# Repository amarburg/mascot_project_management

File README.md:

This repo provides project- and system-level information about the MaSCOT project.  For a high-level overview, see [my blog](http://faculty.washington.edu/amarburg/site/mascot/)

Introduction
------------

The 2016 SEG IR&D Stereo Camera project is supporting the development of a low-cost
stereo camera head in a shallow water enclosure.   The sensor head
will provide stereo video including a dense depth estimate and will include
sufficient on-board processing power for realtime 3D reconstruction.

The sensor head consists of a [Stereolabs
Zed](https://www.stereolabs.com/zed/specs/) USB3 stereo camera and an [NVIdia
Jetson TX1](http://www.nvidia.com/object/jetson-tx1-module.html) embedded
computer.   The Zed consists of a two-camera USB3 sensor unit and a proprietary
set of software libraries for interfacing with the sensor and generating
realtime dense stereo.  These libraries are accelerated using NVidia's CUDA
technology.  The Jetson TX1 computer module contains four 64-bit ARM processor
cores as well as a 256-CUDA core GPU, which allows the Jetson TX1 to run the Zed
processing library.

The Jetson itself lives on a small (approx. credit card) carrier board, but for
development purposes a mini-itx 5" x 5" motherboard is provided which includes a
number of standardized connectors (SATA, Ethernet, SD card, PCI-E, mini-PCI-E)
as well as expansion and debug pin headers.   While the 5"x5" form factor is
somewhat awkward for packaging, the motherboard greatly simplifies the
bootstrapping of new projects.   Given that complete schematics for the
motherboard are available, more application-specific host boards are
theoretically possible.

The underwater enclosure package has a single Subconn 8-pin connector which
provides Cat6 UTP to the sensor head.  This cabling provides gigabit ethernet as
well as 60W power-over-ethernet (PoE).  Note 60W PoE is non-standard. This
connector allows reuse of existing subsea ethernet cables but prevents
supplemental functions going over the same cable (unless we put an Ethernet hub
in the box).      The package also includes two [BlueRobotic Lumen
1](https://www.bluerobotics.com/store/electronics/lumen-light-r1/) submersible
LED lights.

## Other repos

  * https://github.com/amarburg/mascot_companion_board contains schematics and firmware for the Jetson "companion board."

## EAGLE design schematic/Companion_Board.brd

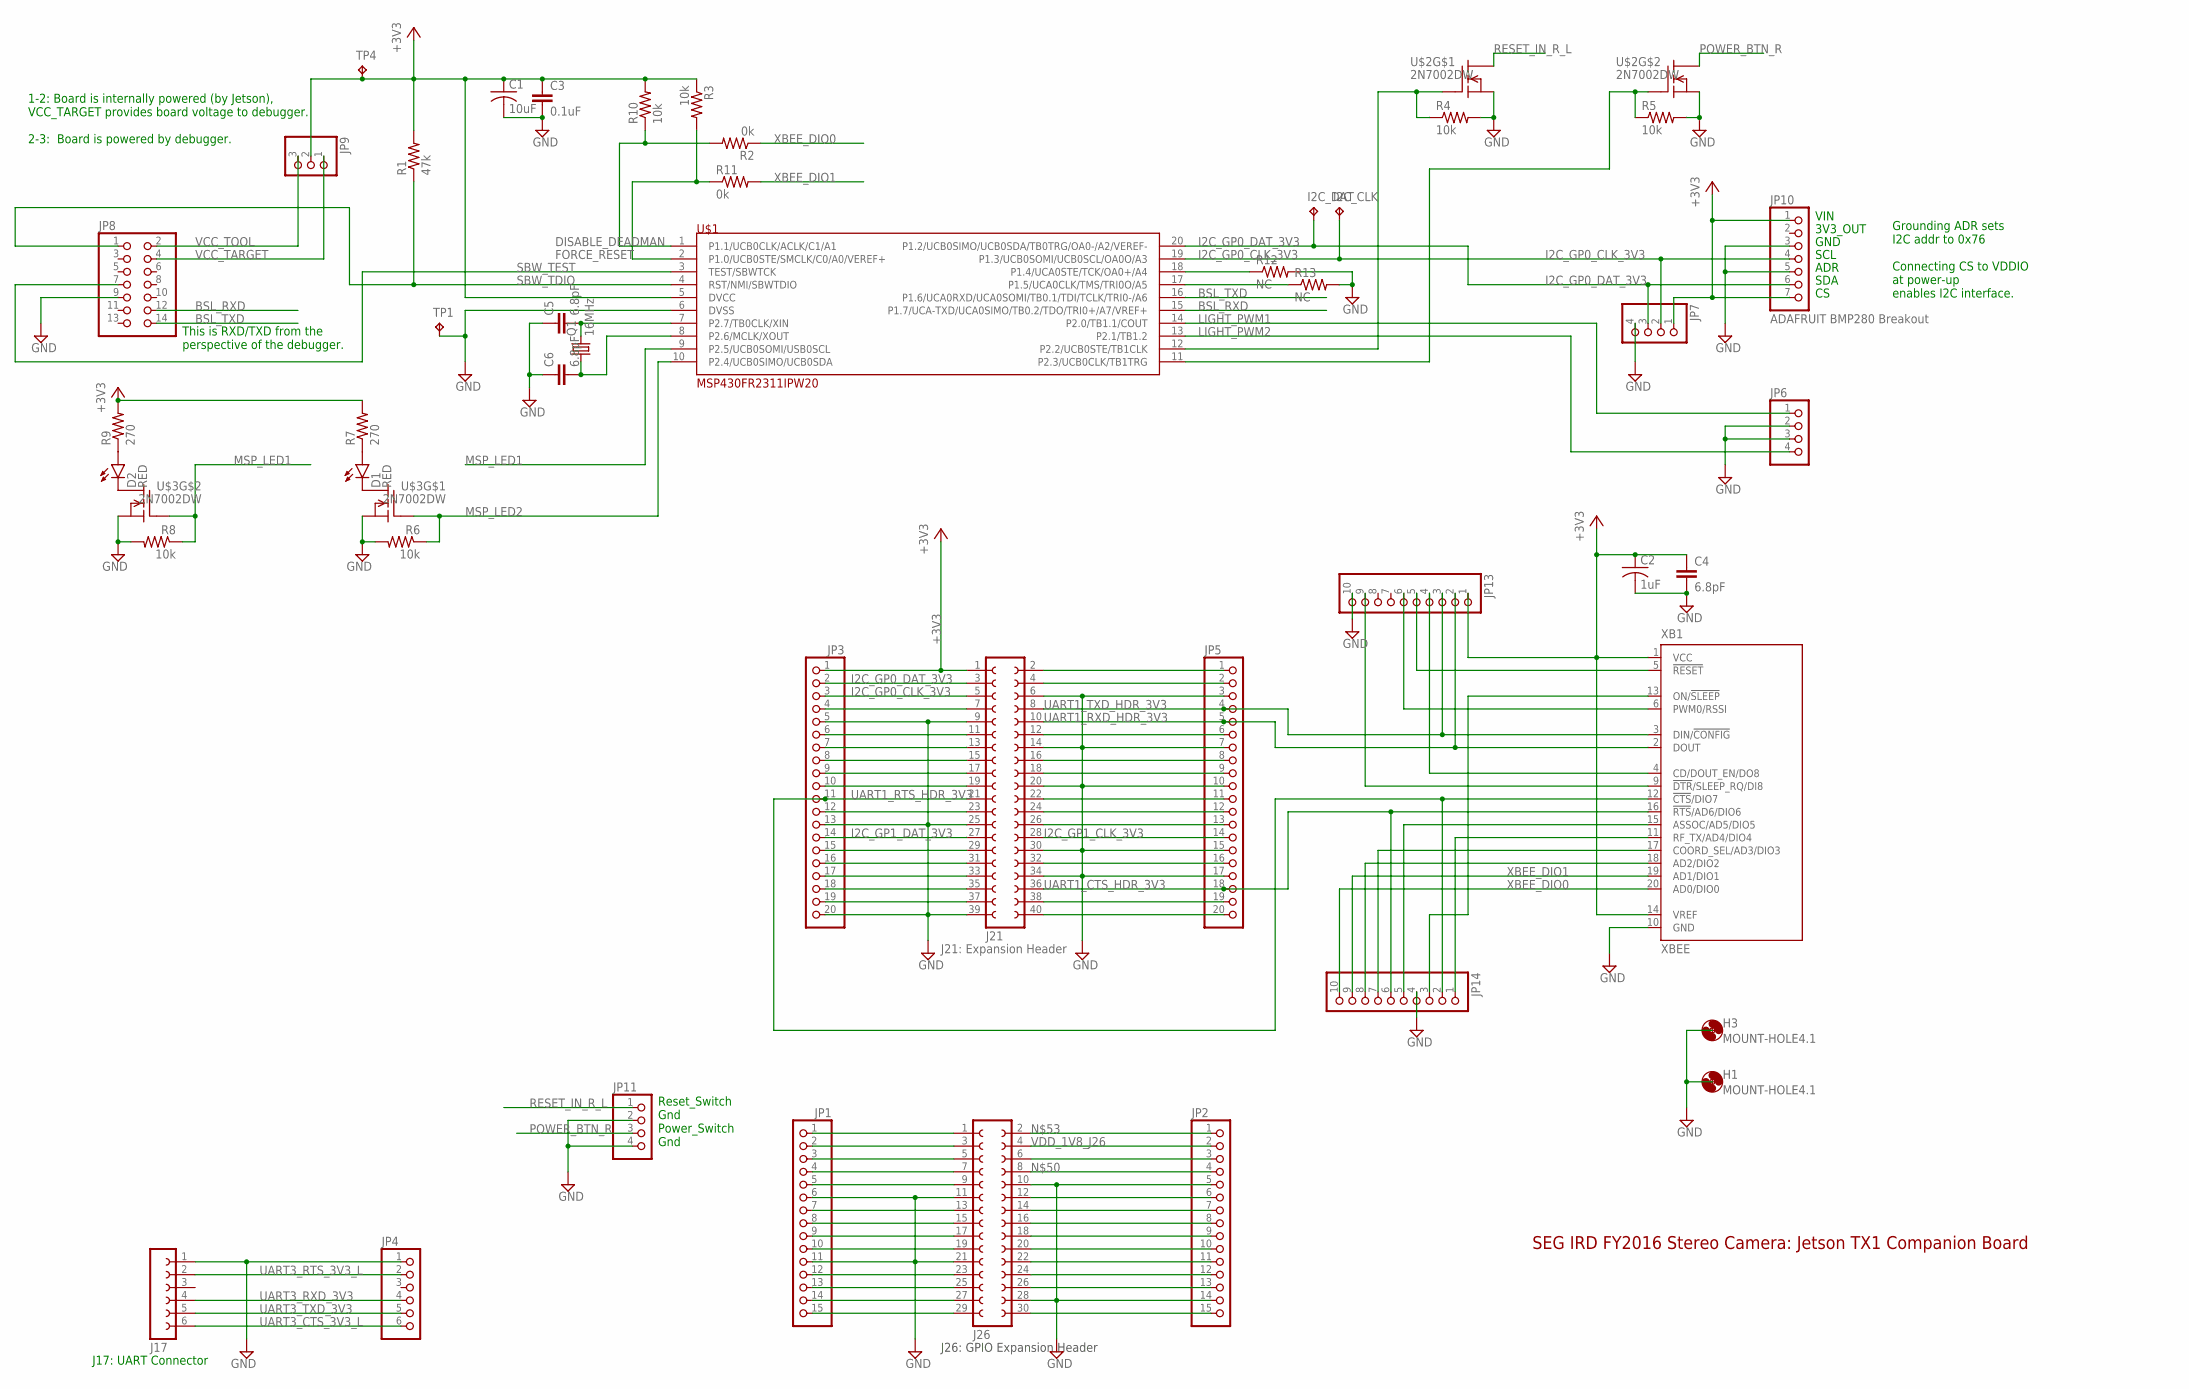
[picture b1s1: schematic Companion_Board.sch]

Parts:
C1: 10uF; C1206
C2: 1uF; C1206
C3: 0.1uF; C0805
C4, C5, C6: 6.8pF; C0805
D1, D2: RED; LED-1206
H1, H3: MOUNT-HOLE4.1; 4,1
I2C_CLK, I2C_DAT: TPPAD1-13; P1-13
J17: FE06-1; FE06
J21: FE20-2
J26: FE15-2
JP1, JP2: PINHD-1X15; 1X15
JP3, JP5: PINHD-1X20; 1X20
JP4: PINHD-1X6; 1X06
JP6, JP11: PINHD-1X4/90; 1X04/90
JP7: PINHD-1X4; 1X04
JP8: PINHD-2X7; 2X07
JP9: PINHD-1X3; 1X03
JP10: ADAFRUIT BMP280 Breakout; 1X07
JP13, JP14: PINHD-1X10; 1X10
Q1: 16MHz; HC49UP
R1: 47k; R0805
R2, R11: 0k; R0805
R3, R4, R5, R6, R8, R10: 10k; R0805
R7, R9: 270; R0805
R12, R13: NC; R0805
TP1, TP4: TPPAD1-13; P1-13
U$1: MSP430FR2311IPW20; SOP65P640X120-20N
U$2, U$3: 2N7002DW; SOT363
XB1: XBEE

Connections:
+3V3: C1.1, C2.1, C3.1, C4.1, J21.1, JP3.1, JP7.1, JP9.2, JP10.1, JP10.7, JP13.1, R1.2, R3.1, R7.2, R9.2, R10.2, TP4.TP, U$1.5 (DVCC), XB1.1 (VCC), XB1.14 (VREF)
BSL_RXD: JP8.12, U$1.15 (P1.7/UCA-TXD/UCA0SIMO/TB0.2/TDO/TRI0+/A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)
BSL_TXD: JP8.14, U$1.16 (P1.6/UCA0RXD/UCA0SOMI/TB0.1/TDI/TCLK/TR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)
DISABLE_DEADMAN: R2.2, R10.1, U$1.1 (P1.1/UCB0CLK/ACLK/C1/A1)
FORCE_RESET: R3.2, R11.1, U$1.2 (P1.0/UCB0STE/SMCLK/C0/A0/VEREF+)
GND: C1.2, C2.2, C3.2, C4.2, C5.1, C6.1, J17.1, J21.6, J21.9, J21.14, J21.20, J21.25, J21.30, J21.34, J21.39, J26.10, J26.11, J26.21, J26.28, JP1.6, JP1.11, JP2.5, JP2.14, JP3.5, JP3.13, JP3.20, JP4.1, JP5.3, JP5.7, JP5.10, JP5.15, JP5.17, JP6.2, JP6.3, JP7.4, JP8.9, JP10.3, JP10.5, JP11.2, JP11.4, JP13.10, JP14.4, R4.2, R5.2, R6.2, R8.2, R12.2, R13.2, TP1.TP, U$1.6 (DVSS), U$2.1 (S), U$2.4 (S), U$3.1 (S), U$3.4 (S), XB1.10 (GND)
I2C_GP0_CLK_3V3: I2C_CLK.TP, J21.5, JP3.3, JP7.2, JP10.4, U$1.19 (P1.3/UCB0SOMI/UCB0SCL/OA0O/A3)
I2C_GP0_DAT_3V3: I2C_DAT.TP, J21.3, JP3.2, JP7.3, JP10.6, U$1.20 (P1.2/UCB0SIMO/UCB0SDA/TB0TRG/OA0-/A2/VE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)
I2C_GP1_CLK_3V3: J21.28, JP5.14
I2C_GP1_DAT_3V3: J21.27, JP3.14
LIGHT_PWM1: JP6.1, U$1.14 (P2.0/TB1.1/COUT)
LIGHT_PWM2: JP6.4, U$1.13 (P2.1/TB1.2)
MSP_LED1: R8.1, U$1.9 (P2.5/UCB0SOMI/USB0SCL), U$3.5 (G)
MSP_LED2: R6.1, U$1.10 (P2.4/UCB0SIMO/UCB0SDA), U$3.2 (G)
unnamed: J26.1, JP1.1
unnamed: J26.3, JP1.2
unnamed: J26.5, JP1.3
unnamed: J26.7, JP1.4
unnamed: J26.9, JP1.5
unnamed: J26.13, JP1.7
unnamed: J26.15, JP1.8
unnamed: J26.17, JP1.9
unnamed: J26.19, JP1.10
unnamed: J26.23, JP1.12
unnamed: J26.25, JP1.13
unnamed: J26.27, JP1.14
unnamed: J26.29, JP1.15
unnamed: J26.30, JP2.15
unnamed: J26.26, JP2.13
unnamed: J26.24, JP2.12
unnamed: J26.22, JP2.11
unnamed: J26.20, JP2.10
unnamed: J26.18, JP2.9
unnamed: J26.16, JP2.8
unnamed: J26.14, JP2.7
unnamed: J26.12, JP2.6
unnamed: R12.1, U$1.18 (P1.4/UCA0STE/TCK/OA0+/A4)
unnamed: J21.7, JP3.4
unnamed: J26.6, JP2.3
unnamed: J21.11, JP3.6
unnamed: J21.13, JP3.7
unnamed: J21.15, JP3.8
unnamed: J21.19, JP3.10
unnamed: J21.23, JP3.12
unnamed: R13.1, U$1.17 (P1.5/UCA0CLK/TMS/TRI0O/A5)
unnamed: J21.29, JP3.15
unnamed: J21.31, JP3.16
unnamed: J21.33, JP3.17
unnamed: J21.35, JP3.18
unnamed: J21.37, JP3.19
unnamed: C5.2, Q1.2, U$1.7 (P2.7/TB0CLK/XIN)
unnamed: J21.12, JP5.6
unnamed: J21.16, JP5.8
unnamed: J21.18, JP5.9
unnamed: J21.22, JP5.11
unnamed: J21.24, JP5.12
unnamed: C6.2, Q1.1, U$1.8 (P2.6/MCLK/XOUT)
unnamed: D1.C, U$3.6 (D)
unnamed: J21.32, JP5.16
unnamed: J21.4, JP5.2
unnamed: J21.38, JP5.19
unnamed: J21.40, JP5.20
unnamed: J21.17, JP3.9
unnamed: J26.8, JP2.4
unnamed: J26.2, JP2.1
unnamed: R4.1, U$1.12 (P2.2/UCB0STE/TB1CLK), U$2.2 (G)
unnamed: R5.1, U$1.11 (P2.3/UCB0CLK/TB1TRG), U$2.5 (G)
unnamed: D2.C, U$3.3 (D)
unnamed: JP13.5, XB1.5 (!RESET)
unnamed: JP13.6, XB1.6 (PWM0/RSSI)
unnamed: JP13.4, XB1.4 (CD/DOUT_EN/DO8)
unnamed: JP13.9, XB1.9 (!DTR!/SLEEP_RQ/DI8)
unnamed: JP14.3, XB1.13 (ON/!SLEEP)
unnamed: JP14.5, XB1.15 (ASSOC/AD5/DIO5)
unnamed: JP14.1, XB1.11 (RF_TX/AD4/DIO4)
unnamed: JP14.7, XB1.17 (COORD_SEL/AD3/DIO3)
unnamed: JP14.8, XB1.18 (AD2/DIO2)
unnamed: D1.A, R7.1
unnamed: D2.A, R9.1
POWER_BTN_R: JP11.3, U$2.3 (D)
RESET_IN_R_L: JP11.1, U$2.6 (D)
SBW_TDIO: JP8.1, R1.1, U$1.4 (RST/NMI/SBWTDIO)
SBW_TEST: JP8.7, U$1.3 (TEST/SBWTCK)
SPI_CS1_3V3: J21.26, JP5.13
UART1_CTS_HDR_3V3: J21.36, JP5.18, JP14.6, XB1.16 (!RTS!/AD6/DIO6)
UART1_RTS_HDR_3V3: J21.21, JP3.11, JP14.2, XB1.12 (!CTS!/DIO7)
UART1_RXD_HDR_3V3: J21.10, JP5.5, JP13.2, XB1.2 (DOUT)
UART1_TXD_HDR_3V3: J21.8, JP5.4, JP13.3, XB1.3 (DIN/!CONFIG)
UART3_CTS_3V3_L: J17.6, JP4.6
UART3_RTS_3V3_L: J17.2, JP4.2
UART3_RXD_3V3: J17.4, JP4.4
UART3_TXD_3V3: J17.5, JP4.5
VCC_TARGET: JP8.4, JP9.1
VCC_TOOL: JP8.2, JP9.3
VDD_1V8_J26: J26.4, JP2.2
VDD_5V0_IO_SYS: J21.2, JP5.1
XBEE_DIO0: JP14.10, R2.1, XB1.20 (AD0/DIO0)
XBEE_DIO1: JP14.9, R11.2, XB1.19 (AD1/DIO1)

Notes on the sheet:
J17: UART Connector
J26: GPIO Expansion Header
J21: Expansion Header
3V3_OUT
GND
SCL
ADR
SDA
Grounding ADR sets I2C addr to 0x76 Connecting CS to VDDIO at power-up enables I2C interface.
SEG IRD FY2016 Stereo Camera: Jetson TX1 Companion Board
1-2: Board is internally powered (by Jetson), VCC_TARGET provides board voltage to debugger. 2-3: Board is powered by debugger.
This is RXD/TXD from the perspective of the debugger.
Reset_Switch Gnd Power_Switch Gnd
VIN

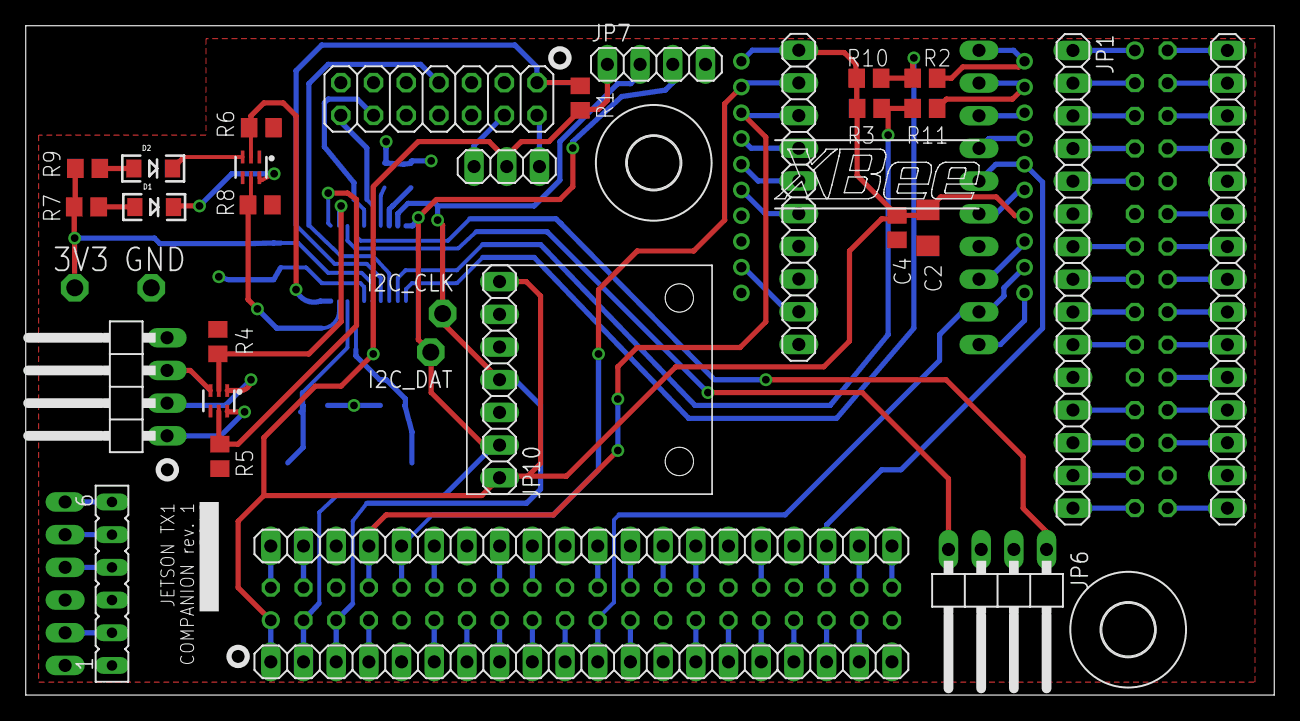
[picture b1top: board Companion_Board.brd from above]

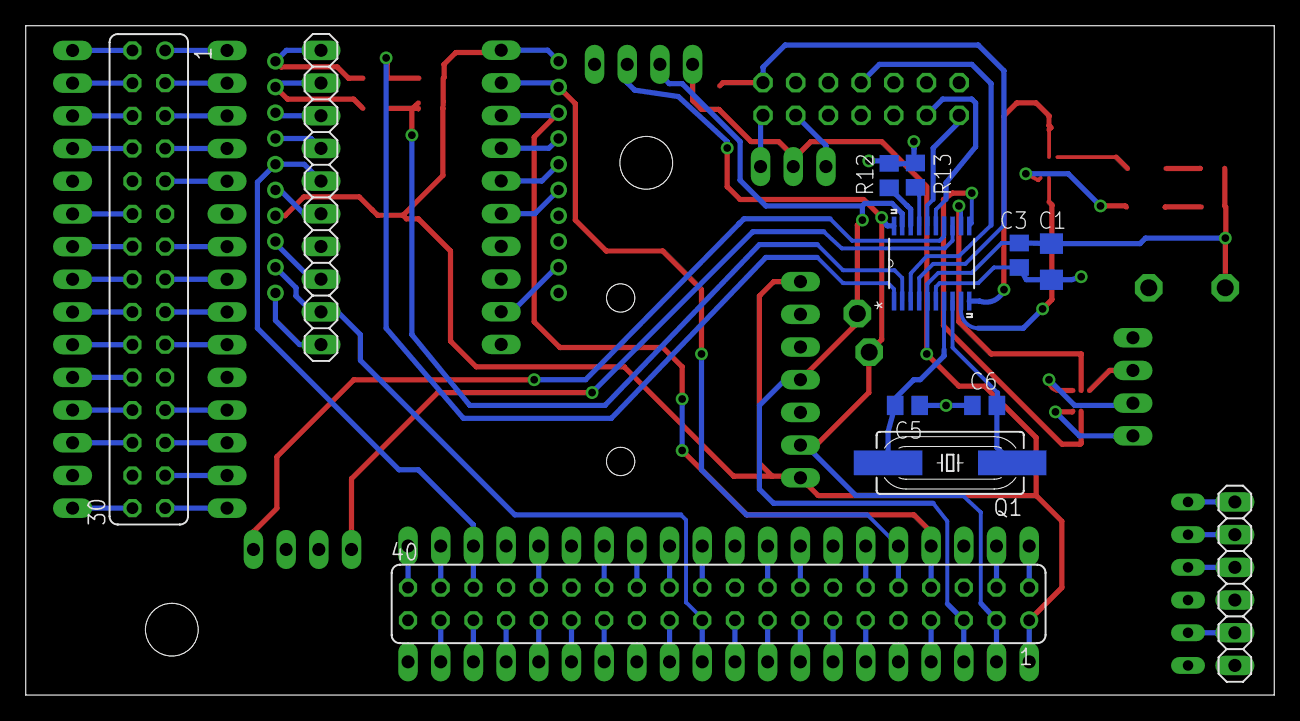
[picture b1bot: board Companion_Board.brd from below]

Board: 2 copper layers, 97.0 x 52.0 mm, 48 parts (12 on the bottom side), 98 nets.

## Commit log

2016-04-28 Initial commit of companion board.
2016-04-29 Iteration on companion board.
2016-04-29 Try building code with ceedling.
2016-05-02 Started README.md
2016-05-02 Damn lack of tables in Bitbucket markdown.
2016-05-02 Changed name to Companion_Board
2016-05-02 Removing "Debug_Port.sch", as it's been renamed.
2016-05-03 Working on Companion board and README.
2016-05-04 Consolidating footprints for companion board.
2016-05-04 Restructured, moved schematics into its own subdir, created firmware directory.
2016-05-04 Added datasheets.
2016-05-04 Updated spec and schematic with pinheaders for reset and power.
2016-05-04 Added picture of Jetson.
2016-05-04 Added mounting holes.
2016-05-05 README.md edited online with Bitbucket
2016-05-06 Working on companion board layout.
2016-05-06 Removed debug connector, now have parts laid out.
2016-05-06 One iteration on board layout.
2016-05-06 First draft of board layout.
2016-05-06 Some corrections to layout.
2016-05-10 Pre-production iteration on companion board, including BOM.
2016-05-11 Updated gerbers.
2016-05-11 Discovered a few non-connected nets.
2016-05-11 Updated schematic with missin serial comms traces to XBee and generated finalized Gerbers.
2016-05-11 Added some relevant gitignores.
2016-05-11 Not sure if I'm doing my TDD correctly...
2016-05-11 Added driver for LEDs.
2016-05-11 Updated schematic based on feedback from FreeDFM
2016-05-11 Now building release version.
2016-05-11 And test version working as well.
2016-05-12 Roughing out some add'l BSP tools.
2016-05-26 Stepping back from Ceedling to a flat Rakefile approach.
2016-05-26 First program with BSP.
2016-05-26 Watchdog test now working.
2016-05-26 Watchdog timer test working.
2016-05-27 Starting to make Rakefile more modular.
2016-05-27 Basic timer test now working.
2016-05-27 Improved on basic timer loop.
2016-05-31 Successfully starting Jetson with MSP430.
2016-05-31 Have basic I2C slave mode working.
2016-05-31 Starting to fill out main app.
2016-06-01 Roughing out state machine.
2016-06-01 Further work on state machine.
2016-06-01 Successful PWM to lights and I2C->PWM connection.
2016-06-02 Working on DIO testing. Unable to pass DIO through XBee.
2016-06-02 Updated README with current status rel to specification.
2016-07-29 Implemented basic state machine.
2016-07-29 Started on ECO2
2016-07-29 First rev on change order #2
2016-07-29 Iteration on ECO #2
2016-07-29 Moved jetson temperature and recorder performance into the mascot repo.
2016-07-29 Folded the jetson_common repo into the mascot repo.
2016-07-29 Plugged in firm quote from Ocean Innovations.
2016-08-01 Working on ECO #2
2016-08-01 Added total value to Mascot ECO #2
2016-10-26 Split the monolithic repo into separate repos.
2016-10-26 Updated README to reflect split repos.
2016-10-26 Removed companiond code that's not needed.
2016-10-26 Split documents into their own directories, commited PDF copies.
2016-10-26 Added a few photos from the Google Drive.
2016-10-26 Added bill of materials for EC002 from the Google Drive.
2016-10-26 Changed permissions on a couple of images.
2016-10-26 Added data sheets.
2016-10-26 Added block diagrams.

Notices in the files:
parts and their libraries:
SparkFun-LED: Licensing: Creative Commons ShareAlike 4.0 International - https://creativecommons.org/licenses/by-sa/4.0
